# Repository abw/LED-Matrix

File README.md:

# LED-Matrix
This project contains design templates, schematics, PCB layouts and
other resources for the construction of an LED Matrix

Watch the YouTube video series:

* [Part 1](https://www.youtube.com/watch?v=AXzYg67qcFU)
* [Part 2](https://www.youtube.com/watch?v=oouwt-w1FjE)
* [Part 3](https://www.youtube.com/watch?v=P1SUvm24y38)
* [Part 4](https://www.youtube.com/watch?v=9LTRPMgsqeI)

The [documents](documents) directory contains plans, templates, cutting
guides, etc.

See the [hardware](hardware) directory for the
schematics and board designs for the [power distribution board](hardware/Power%20Board/v1.2)
and the main [control board](hardware/Control%20Board/v1.0).

The [arduino](arduino) directory contains the source code for Arduino firmware.
This includes the examples that are shown in part 4 of the video series.

The [sketchup](sketchup) directory contains a CAD design of the LED
Matrix created in Sketchup.

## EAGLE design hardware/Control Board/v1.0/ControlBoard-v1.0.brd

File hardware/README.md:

# LED-Matrix Hardware
This directory contains the Eagle schematics, board designs and Gerber
files for the LED Matrix.

The [Power Board](Power%20Board/v1.2) is a power distribution module
that hosts 3 MP1584EN buck regulator modules.  These provide power for
the LED strips.

The [Control Board](Control%20Board/v1.0) is a board which can be used
as an all-in-one Arduino shield, or as a pair of mother/daughter boards.
It provides a connection to the Power Board to receive power and return
data for the LED strips.  It also has 4 connectors for push-button
switches with integrated LEDs in the bezel.

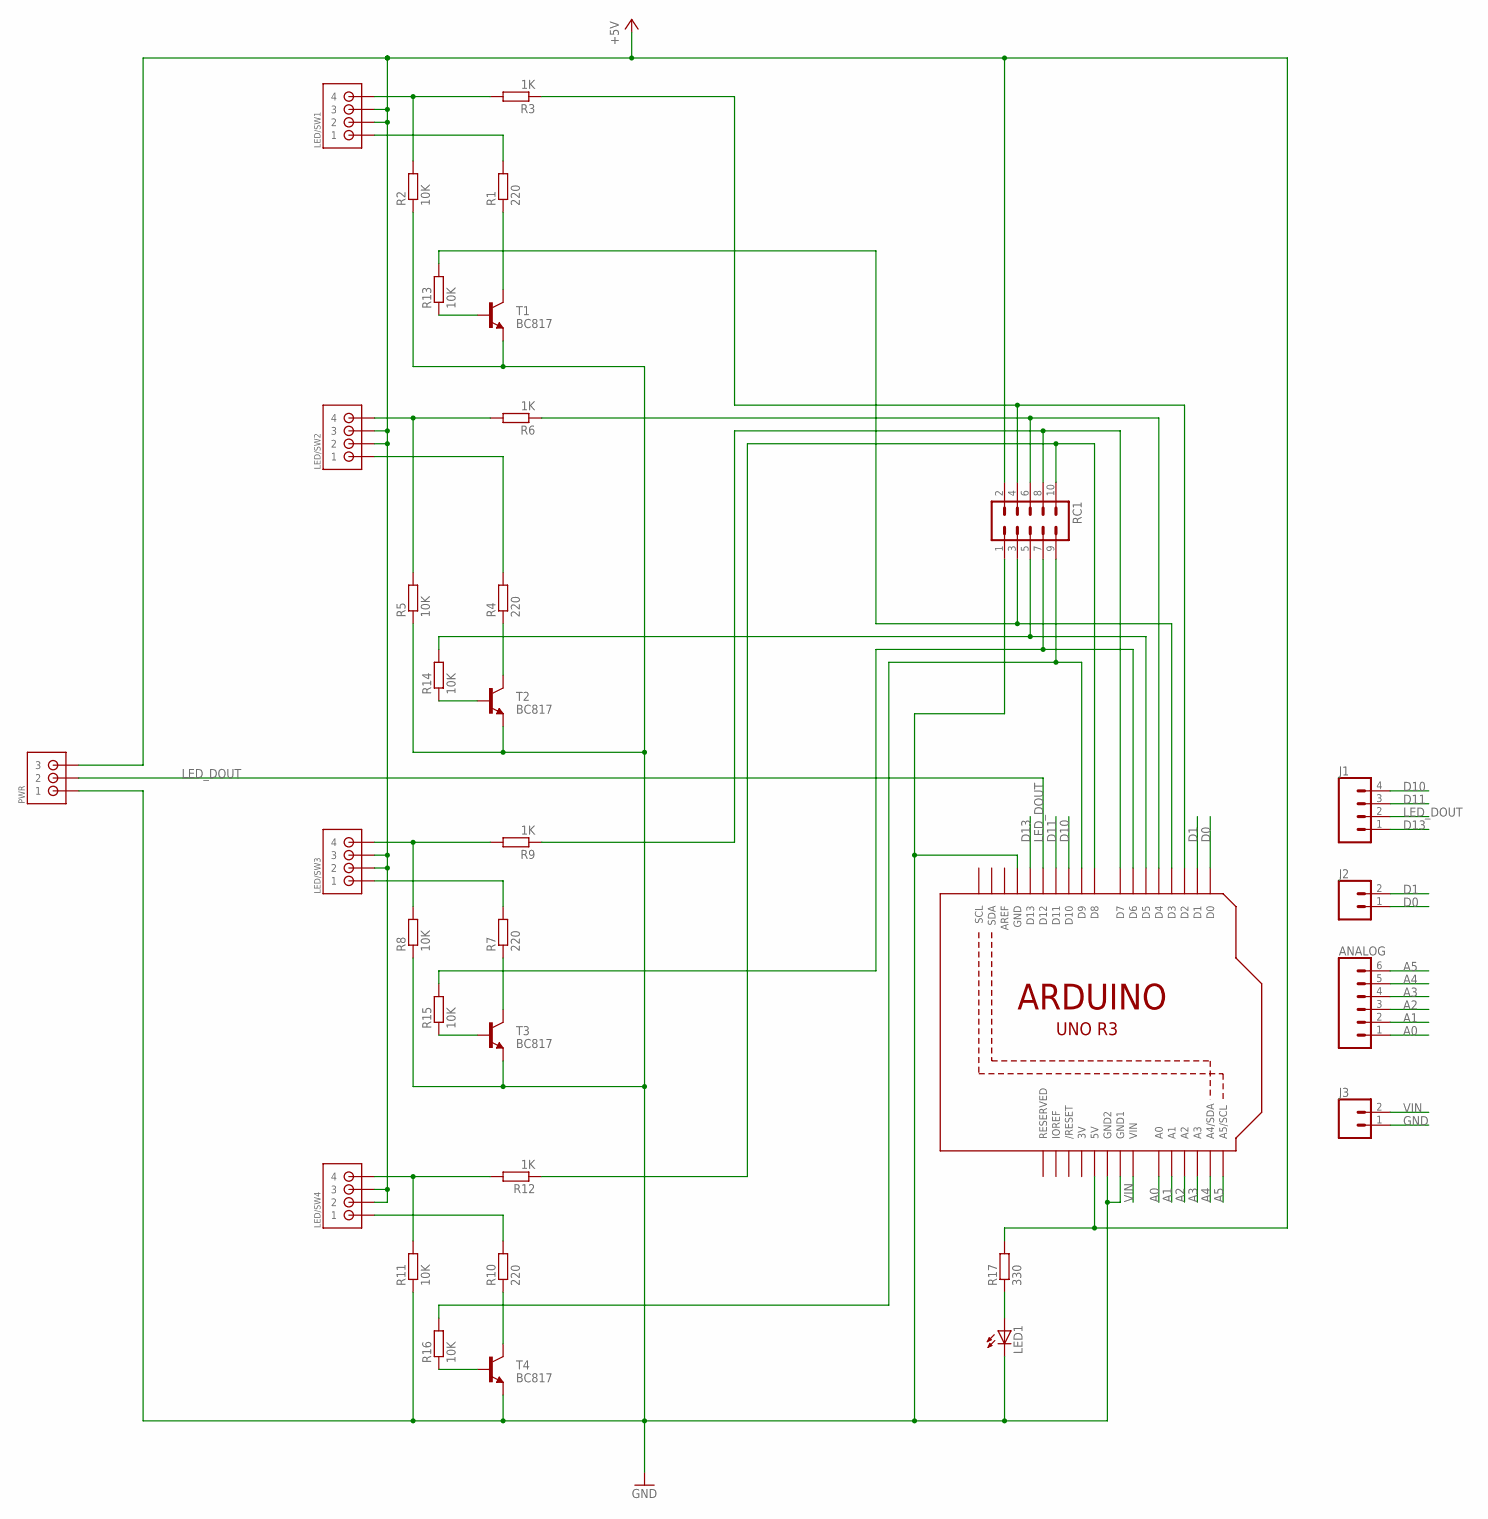
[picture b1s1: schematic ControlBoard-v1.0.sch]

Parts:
ANALOG: CONN_06SILK_FEMALE_PTH; 1X06
J1: CONN_04; 1X04
J2, J3: CONN_02; 1X02
LED1: LEDCHIPLED_0805; CHIPLED_0805
LED/SW1, LED/SW2, LED/SW3, LED/SW4: JST-XA-04-PIN; JST-XA-04
PWR: JST-XA-03-PIN; JST-XA-03
R1, R4, R7, R10: 220; R0805
R2, R5, R8, R11, R13, R14, R15, R16: 10K; R0805
R3, R6, R9, R12: 1K; R0805
R17: 330; R0805
RC1: ML10
T1, T2, T3, T4: BC817; SOT23
U1: ARDUINO-SHIELDLET; ARDUINOR3-PINS

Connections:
3V: U1.3V
+5V: LED/SW1.2, LED/SW1.3, LED/SW2.2, LED/SW2.3, LED/SW3.2, LED/SW3.3, LED/SW4.2, LED/SW4.3, PWR.3, R17.2, RC1.2, U1.5V
A0: ANALOG.1, U1.A0
A1: ANALOG.2, U1.A1
A2: ANALOG.3, U1.A2
A3: ANALOG.4, U1.A3
A4: ANALOG.5, U1.A4 (A4/SDA)
A5: ANALOG.6, U1.A5 (A5/SCL)
D0: J2.1, U1.D0
D1: J2.2, U1.D1
D10: J1.4, U1.D10
D11: J1.3, U1.D11
D13: J1.1, U1.D13
GND: J3.1, LED1.C, PWR.1, R2.1, R5.1, R8.1, R11.1, RC1.1, T1.2 (E), T2.2 (E), T3.2 (E), T4.2 (E), U1.GND, U1.GND1, U1.GND2
LED_DOUT: J1.2, PWR.2, U1.D12
unnamed: LED/SW1.1, R1.2
unnamed: R1.1, T1.3 (C)
unnamed: LED/SW1.4, R2.2, R3.2
unnamed: R3.1, RC1.4, U1.D2
unnamed: R13.1, T1.1 (B)
unnamed: LED/SW2.1, R4.2
unnamed: R4.1, T2.3 (C)
unnamed: LED/SW2.4, R5.2, R6.2
unnamed: R6.1, RC1.6, U1.D4
unnamed: R14.2, RC1.5, U1.D5
unnamed: LED/SW3.1, R7.2
unnamed: R7.1, T3.3 (C)
unnamed: LED/SW3.4, R8.2, R9.2
unnamed: R9.1, RC1.8, U1.D7
unnamed: R15.2, RC1.7, U1.D6
unnamed: LED/SW4.1, R10.2
unnamed: R10.1, T4.3 (C)
unnamed: LED/SW4.4, R11.2, R12.2
unnamed: R12.1, RC1.10, U1.D8
unnamed: R16.2, RC1.9, U1.D9
unnamed: R14.1, T2.1 (B)
unnamed: R15.1, T3.1 (B)
unnamed: R16.1, T4.1 (B)
unnamed: LED1.A, R17.1
unnamed: R13.2, RC1.3, U1.D3
VIN: J3.2, U1.VIN

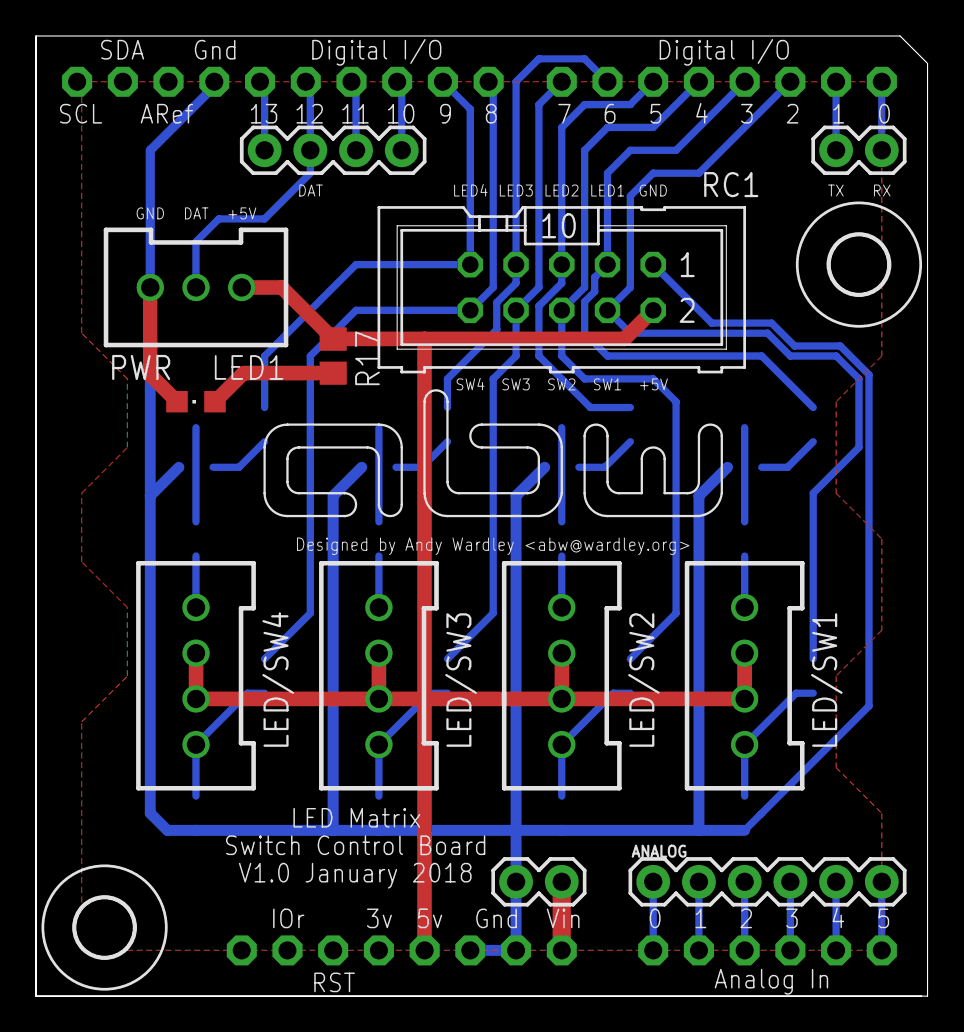
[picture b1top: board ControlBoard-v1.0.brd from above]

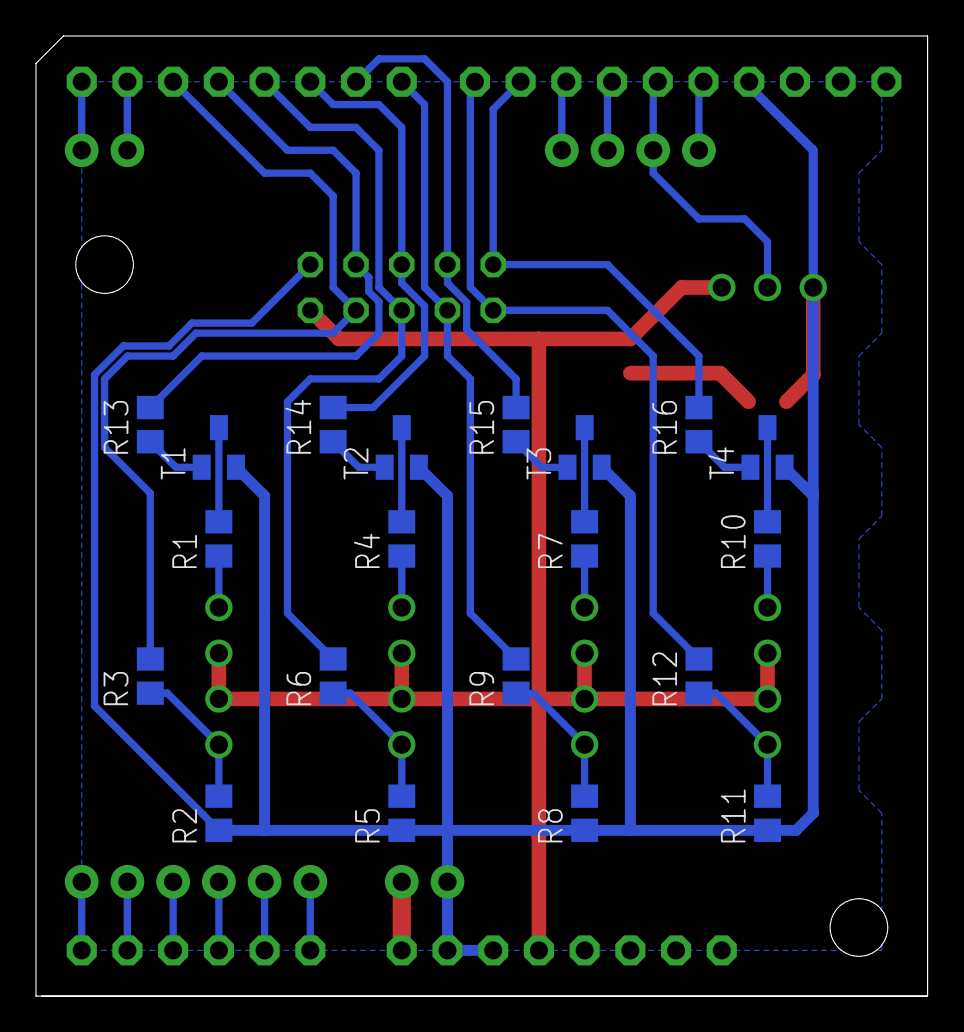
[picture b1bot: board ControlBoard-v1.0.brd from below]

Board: 2 copper layers, 49.5 x 53.3 mm, 36 parts (20 on the bottom side), 40 nets.

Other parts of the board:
U$2, U$3: 3,2
U$4: ABWLOGO-TINY

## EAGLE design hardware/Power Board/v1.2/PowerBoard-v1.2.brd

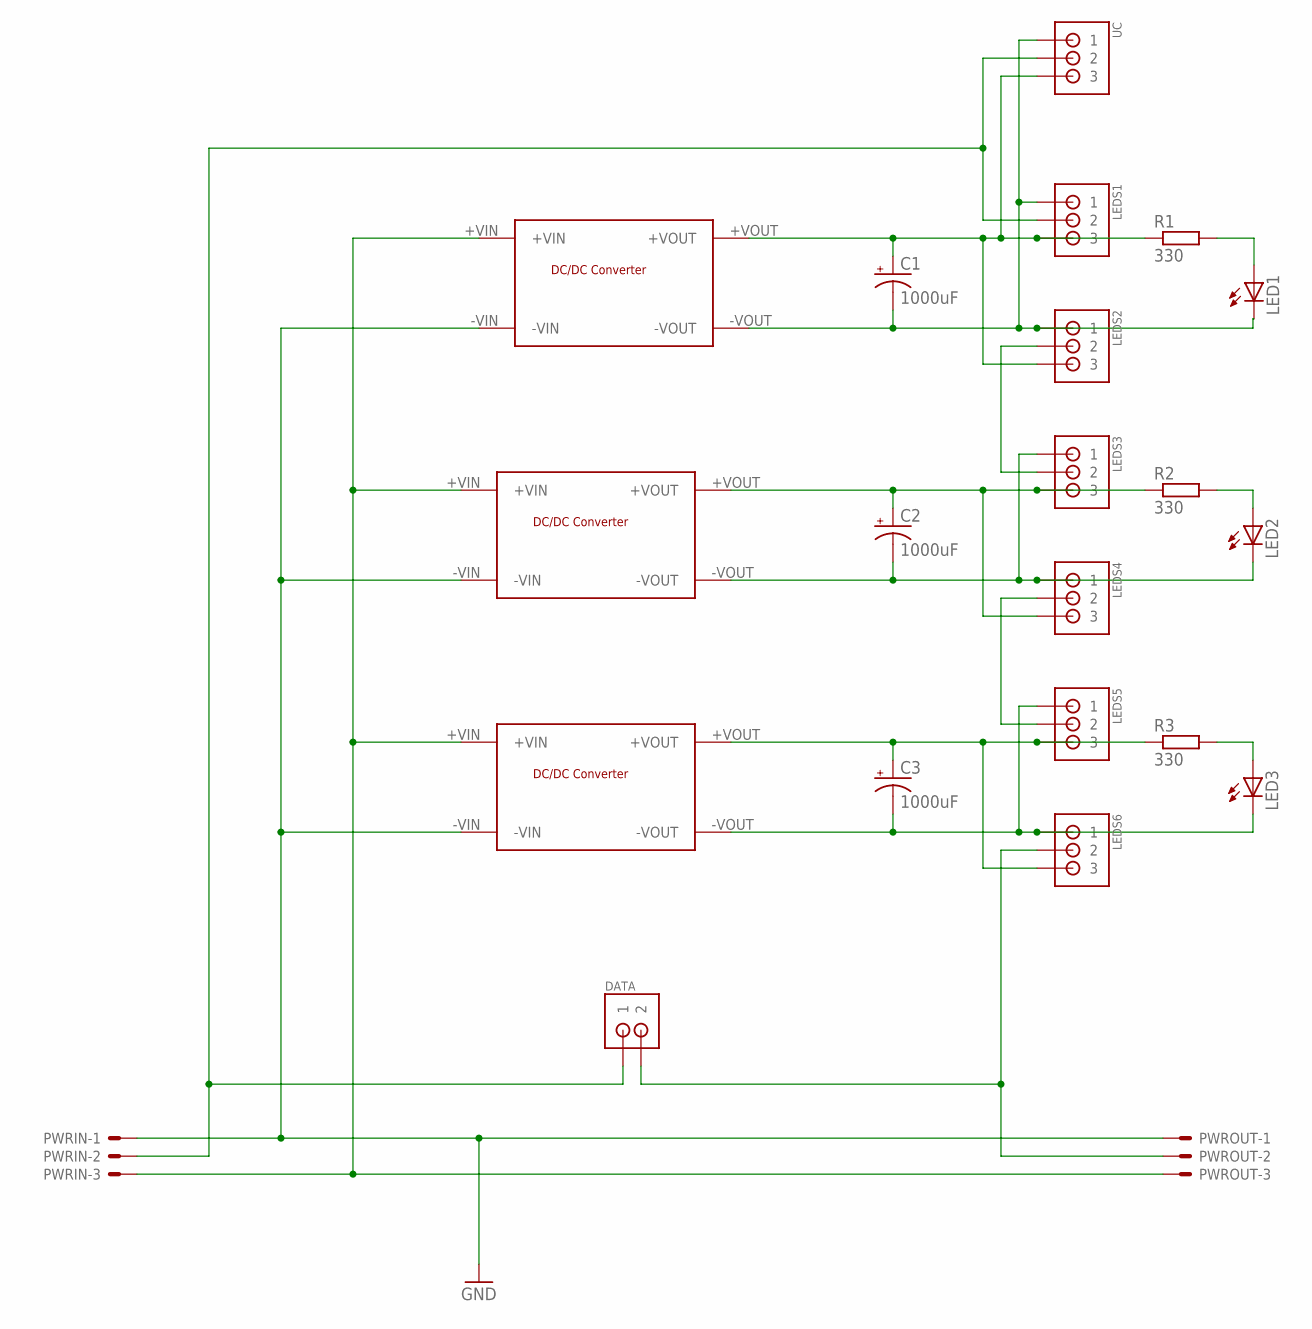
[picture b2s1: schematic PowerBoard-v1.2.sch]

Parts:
C1, C2, C3: 1000uF; CPOL-RADIAL-1000UF-25V
DATA: JST-XA-02-PIN; JST-XA-02
LED1, LED2, LED3: LEDCHIP-LED0805; CHIP-LED0805
LEDS1, LEDS2, LEDS3, LEDS4, LEDS5, LEDS6: JST-XA-03-PIN; JST-XA-03
PWRIN: KK-156-3
PWROUT: KK-156-3
R1, R2, R3: 330; M0805
U$1, U$2, U$3: DC-DC-CONVERTER; MP1584EN-BUCK-CONVERTER
UC: JST-XA-03-PIN; JST-XA-03

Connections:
DATIN: DATA.1, LEDS1.2, PWRIN.2, UC.2
DATOUT: DATA.2, LEDS6.2, PWROUT.2
GND: PWRIN.1, PWROUT.1, U$1.-VIN, U$2.-VIN, U$3.-VIN
GNDOUT1: C1.-, LED1.C, LEDS1.1, LEDS2.1, U$1.-VOUT, UC.1
GNDOUT2: C2.-, LED2.C, LEDS3.1, LEDS4.1, U$2.-VOUT
GNDOUT3: C3.-, LED3.C, LEDS5.1, LEDS6.1, U$3.-VOUT
unnamed: LED1.A, R1.2
unnamed: LED2.A, R2.2
unnamed: LEDS2.2, LEDS3.2
unnamed: LEDS4.2, LEDS5.2
unnamed: LED3.A, R3.2
VIN: PWRIN.3, PWROUT.3, U$1.+VIN, U$2.+VIN, U$3.+VIN
VOUT1: C1.+, LEDS1.3, LEDS2.3, R1.1, U$1.+VOUT, UC.3
VOUT2: C2.+, LEDS3.3, LEDS4.3, R2.1, U$2.+VOUT
VOUT3: C3.+, LEDS5.3, LEDS6.3, R3.1, U$3.+VOUT

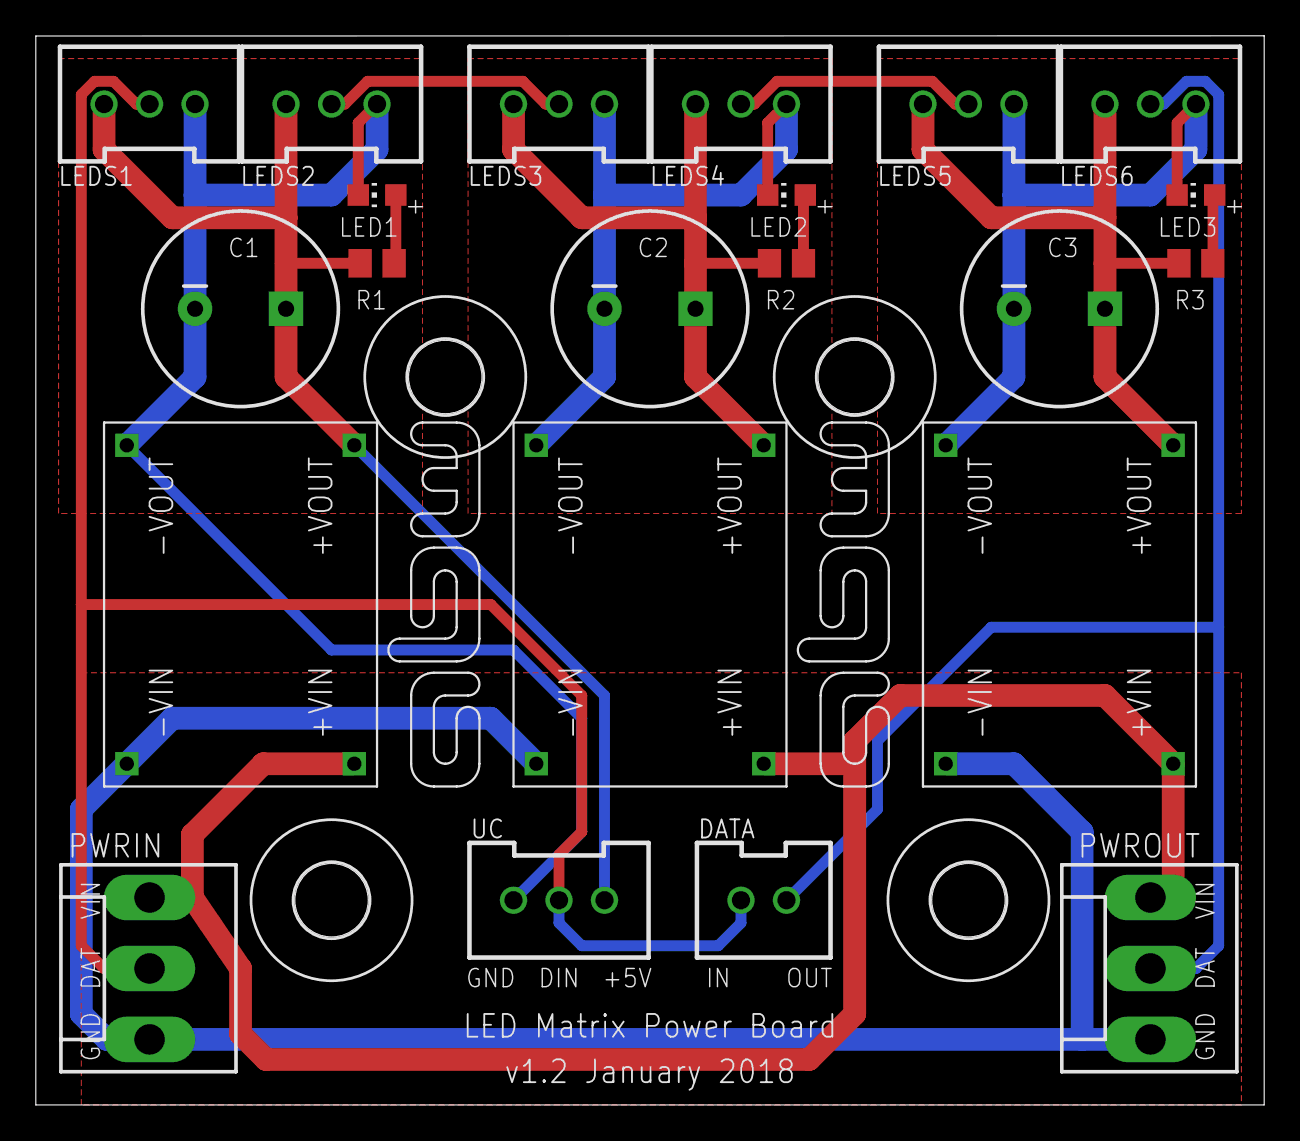
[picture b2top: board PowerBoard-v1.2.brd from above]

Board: 2 copper layers, 68.6 x 59.7 mm, 29 parts (1 on the bottom side), 15 nets.

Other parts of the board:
U$4, U$5, U$6, U$7: 4,1
U$8: ABWLOGO-SMALL
U$9, U$10: ABWLOGO-MICRO

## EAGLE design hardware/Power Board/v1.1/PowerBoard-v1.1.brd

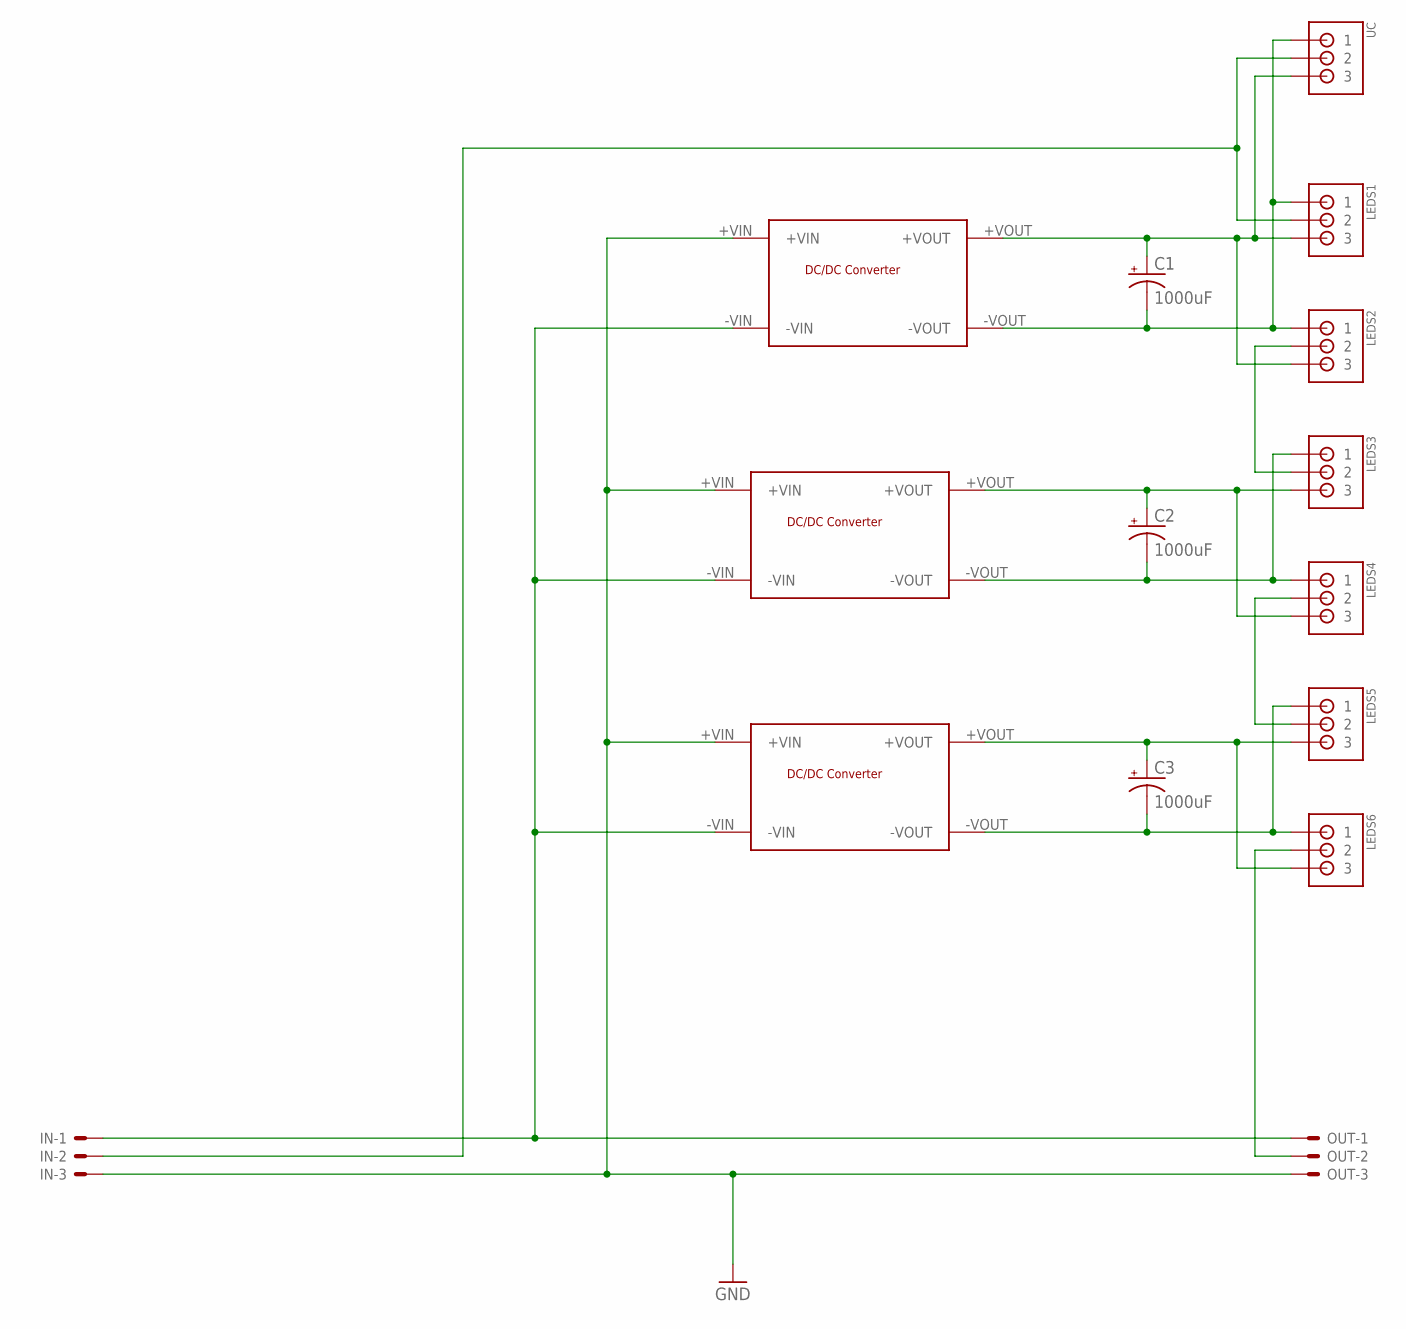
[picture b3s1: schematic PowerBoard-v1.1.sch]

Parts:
C1, C2, C3: 1000uF; CPOL-RADIAL-1000UF-25V
IN: 22-23-2031
LEDS1, LEDS2, LEDS3, LEDS4, LEDS5, LEDS6: JST-XA-03-PIN; JST-XA-03
OUT: 22-23-2031
U$1, U$2, U$3: DC-DC-CONVERTER; MP1584EN-BUCK-CONVERTER
UC: JST-XA-03-PIN; JST-XA-03

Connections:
GND: IN.3, OUT.3, U$1.+VIN, U$2.+VIN, U$3.+VIN
unnamed: IN.1, OUT.1, U$1.-VIN, U$2.-VIN, U$3.-VIN
unnamed: C1.-, LEDS1.1, LEDS2.1, U$1.-VOUT, UC.1
unnamed: C1.+, LEDS1.3, LEDS2.3, U$1.+VOUT, UC.3
unnamed: C2.+, LEDS3.3, LEDS4.3, U$2.+VOUT
unnamed: C2.-, LEDS3.1, LEDS4.1, U$2.-VOUT
unnamed: C3.+, LEDS5.3, LEDS6.3, U$3.+VOUT
unnamed: C3.-, LEDS5.1, LEDS6.1, U$3.-VOUT
unnamed: IN.2, LEDS1.2, UC.2
unnamed: LEDS2.2, LEDS3.2
unnamed: LEDS4.2, LEDS5.2
unnamed: LEDS6.2, OUT.2

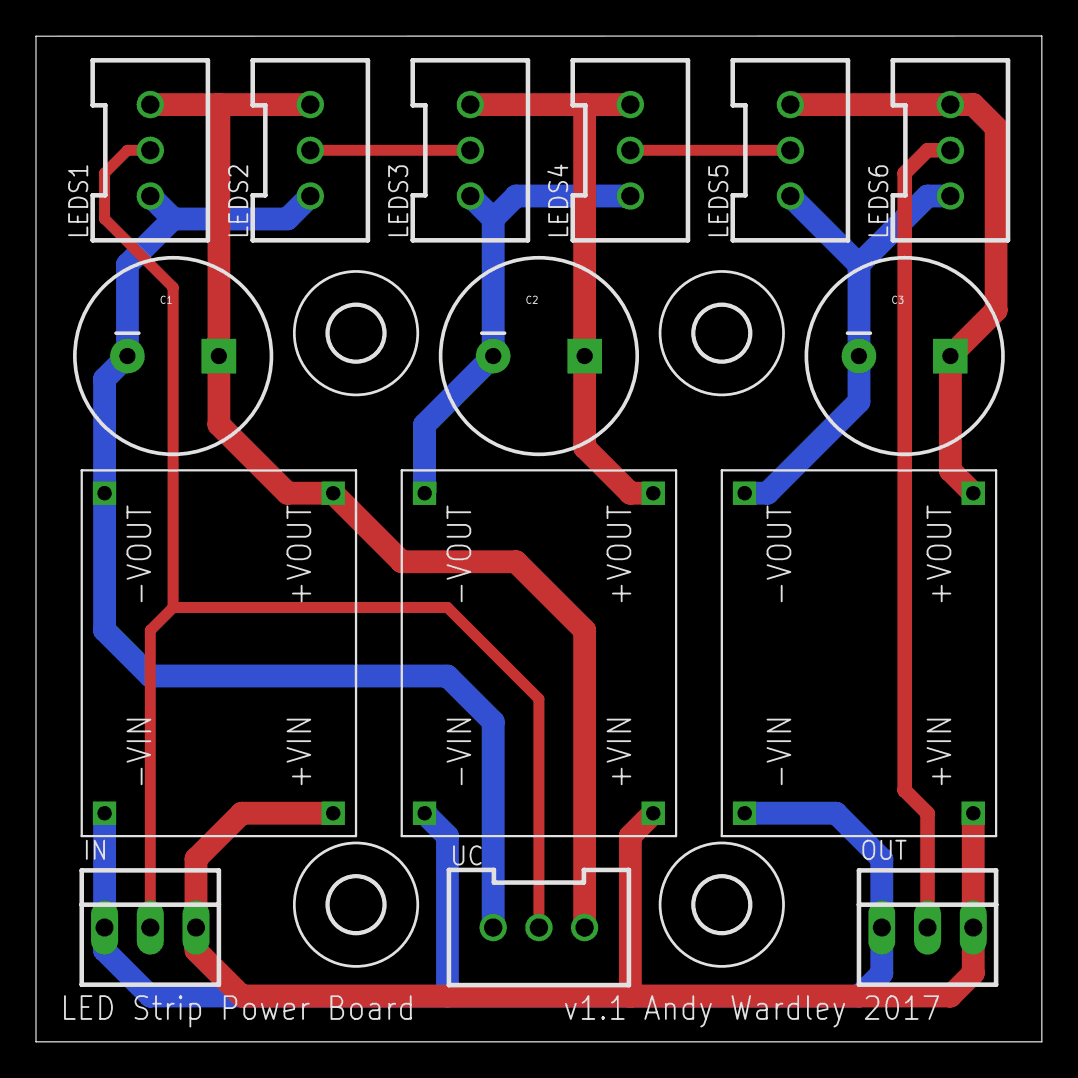
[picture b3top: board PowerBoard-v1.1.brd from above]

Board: 2 copper layers, 55.9 x 55.9 mm, 19 parts (0 on the bottom side), 12 nets.

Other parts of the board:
U$4, U$5, U$6, U$7: 3,0

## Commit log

2017-12-21 Added documents, power board design and test firmware
2017-12-21 Fixed link typo
2018-02-13 Added LED-Demo1 files
2018-02-16 Added templates for dividers and side panel
2018-02-16 Added sketchup model
2018-02-16 Added arduino demo code
2018-02-16 Added .gitignore
2018-02-16 Disabled some debugging statements
2018-02-16 Tidied up some comments, disabled some debugging
2018-02-16 Fixed comments
2018-02-21 Added new test/demo files
2018-02-21 Added tmp to .gitignore
2018-02-21 Reorganised example 1
2018-02-21 Reset width/height
2018-02-21 Changed LEDMatrix to return CRGB reference
2018-02-21 Tweaked comments
2018-02-22 Updated tests
2018-02-22 Added schematics and board layout for new power module (v1.2)
2018-02-22 Added files for Control Board

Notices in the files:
parts and their libraries:
SparkFun-Connectors: Licensing: Creative Commons ShareAlike 4.0 International - https://creativecommons.org/licenses/by-sa/4.0
